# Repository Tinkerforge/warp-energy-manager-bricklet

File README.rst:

WARP Energy Manager Bricklet
============================

This Bricklet together with the ESP32 Ethernet Brick form the
hardware used in the WARP Energy Manager.

See https://www.warp-charger.com/energy-manager.html for more details

This repository contains the firmware source code and the hardware design
files. The documentation generator configs can be found at
https://github.com/Tinkerforge/generators

.. BEGIN WARP REPOSITORIES (managed block, generated from esp32-firmware/repo_overview.rst - do not edit by hand, run update_repo_overview.py instead)

WARP Repositories
-----------------

This is an overview of all repositories that make up the WARP Charger and
WARP Energy Manager ecosystem.

Please report **any** issue concerning WARP hard- or software in the
`esp32-firmware`_ repository, no matter which repository it originates from.

Software
~~~~~~~~

- `esp32-firmware`_ - Source code of the ESP32 firmware shared between all WARP Chargers and Energy Managers

Libraries used by the firmware:

- `tfjson`_ - SAX style JSON serializer and deserializer
- `tfnetwork`_ - Modbus TCP server and client implementation
- `tfocpp`_ - OCPP 1.6 implementation
- `tftools`_ - Miscellaneous tools and helpers

Remote access:

- `esp32-remote-access`_ - Source code of the my.warp-charger.com remote access server

Documentation, tools and integrations:

- `warp-charger`_ - Source code of (docs.)warp-charger.com and the printed manual, released firmwares, datasheets and documents, as well as some tools and hardware design files
- `api.warp-charger.com`_ - Serves APIs that are used by WARP Chargers to obtain relevant public information like day ahead prices
- `vislog.warp-charger.com`_ - Visualizes WARP Charger logs and EVSE debug protocols
- `dbus-warp-charger`_ - Integrates WARP Chargers into a Victron Energy Venus OS device (e.g. Cerbo GX)

WARP Charger Hardware
~~~~~~~~~~~~~~~~~~~~~~

WARP4 Charger
"""""""""""""

*Current charger generation.*

- `warp-esp32-ethernet-v2-brick`_ - Hardware design files of the WARP ESP32 Ethernet Brick 2.0
- `warp-esp32-ethernet-v2-co-bricklet`_ - Firmware source code of the WARP ESP32 Ethernet 2.0 Co Bricklet (co-processor)
- `evse-v4-bricklet`_ - Hardware design files of the EVSE 4.0 Bricklet (firmware shared with the EVSE 2.0 Bricklet)
- `nfc-bricklet`_ - Firmware source code and hardware design files of the NFC Bricklet

WARP3 Charger
"""""""""""""

- `warp-esp32-ethernet-brick`_ - Hardware design files of the WARP ESP32 Ethernet Brick
- `evse-v3-bricklet`_ - Hardware design files of the EVSE 3.0 Bricklet (firmware shared with the EVSE 2.0 Bricklet)
- `nfc-bricklet`_ - Firmware source code and hardware design files of the NFC Bricklet

WARP2 Charger
"""""""""""""

- `esp32-ethernet-brick`_ - Hardware design files of the ESP32 Ethernet Brick
- `evse-v2-bricklet`_ - Firmware source code and hardware design files of the EVSE 2.0 Bricklet
- `nfc-bricklet`_ - Firmware source code and hardware design files of the NFC Bricklet

WARP1 Charger
"""""""""""""

- `esp32-brick`_ - Hardware design files of the ESP32 Brick
- `evse-bricklet`_ - Firmware source code and hardware design files of the EVSE Bricklet
- `rs485-bricklet`_ - Firmware source code and hardware design files of the RS485 Bricklet

WARP Energy Manager Hardware
~~~~~~~~~~~~~~~~~~~~~~~~~~~~~~

WARP Energy Manager 2.0
"""""""""""""""""""""""

*Current energy manager generation.*

- `esp32-ethernet-brick`_ - Hardware design files of the ESP32 Ethernet Brick
- `warp-energy-manager-v2-bricklet`_ - Firmware source code and hardware design files of the WARP Energy Manager 2.0 Bricklet
- `warp-front-panel-bricklet`_ - Firmware source code and hardware design files of the WARP Front Panel Bricklet

WARP Energy Manager 1.0
"""""""""""""""""""""""

- `esp32-ethernet-brick`_ - Hardware design files of the ESP32 Ethernet Brick
- `warp-energy-manager-bricklet`_ - Firmware source code and hardware design files of the WARP Energy Manager Bricklet

Forked/patched projects
~~~~~~~~~~~~~~~~~~~~~~~~~

- `arduino-esp32`_
- `esp32-arduino-libs`_
- `WireGuard-ESP32-Arduino`_

.. Link targets: One definition per repository, keep in sync with the lists above.

.. _esp32-firmware: https://github.com/Tinkerforge/esp32-firmware
.. _tfjson: https://github.com/Tinkerforge/tfjson
.. _tfnetwork: https://github.com/Tinkerforge/tfnetwork
.. _tfocpp: https://github.com/Tinkerforge/tfocpp
.. _tftools: https://github.com/Tinkerforge/tftools
.. _esp32-remote-access: https://github.com/Tinkerforge/esp32-remote-access
.. _warp-charger: https://github.com/Tinkerforge/warp-charger
.. _api.warp-charger.com: https://github.com/Tinkerforge/api.warp-charger.com
.. _vislog.warp-charger.com: https://github.com/Tinkerforge/vislog.warp-charger.com
.. _dbus-warp-charger: https://github.com/Tinkerforge/dbus-warp-charger
.. _warp-esp32-ethernet-v2-brick: https://github.com/Tinkerforge/warp-esp32-ethernet-v2-brick
.. _warp-esp32-ethernet-v2-co-bricklet: https://github.com/Tinkerforge/warp-esp32-ethernet-v2-co-bricklet
.. _evse-v4-bricklet: https://github.com/Tinkerforge/evse-v4-bricklet
.. _nfc-bricklet: https://github.com/Tinkerforge/nfc-bricklet
.. _warp-esp32-ethernet-brick: https://github.com/Tinkerforge/warp-esp32-ethernet-brick
.. _evse-v3-bricklet: https://github.com/Tinkerforge/evse-v3-bricklet
.. _esp32-ethernet-brick: https://github.com/Tinkerforge/esp32-ethernet-brick
.. _evse-v2-bricklet: https://github.com/Tinkerforge/evse-v2-bricklet
.. _esp32-brick: https://github.com/Tinkerforge/esp32-brick
.. _evse-bricklet: https://github.com/Tinkerforge/evse-bricklet
.. _rs485-bricklet: https://github.com/Tinkerforge/rs485-bricklet
.. _warp-energy-manager-v2-bricklet: https://github.com/Tinkerforge/warp-energy-manager-v2-bricklet
.. _warp-front-panel-bricklet: https://github.com/Tinkerforge/warp-front-panel-bricklet
.. _warp-energy-manager-bricklet: https://github.com/Tinkerforge/warp-energy-manager-bricklet
.. _arduino-esp32: https://github.com/Tinkerforge/arduino-esp32
.. _esp32-arduino-libs: https://github.com/Tinkerforge/esp32-arduino-libs
.. _WireGuard-ESP32-Arduino: https://github.com/Tinkerforge/WireGuard-ESP32-Arduino

.. END WARP REPOSITORIES

Repository Content
------------------

software/:
 * examples/: Examples for all supported languages
 * build/: Compiled files
 * src/: Source code of firmware
 * Makefile: Makefile to build project

hardware/:
 * Contains KiCad project files and additionally schematics as PDF

datasheets/:
 * Contains datasheets for sensors and complex ICs that are used

Hardware
--------

The hardware is designed with the open source EDA Suite KiCad
(http://www.kicad.org). Before you are able to open the files,
you have to install the Tinkerforge kicad-libraries
(https://github.com/Tinkerforge/kicad-libraries). You can either clone
them directly in hardware/ or clone them in a separate folder and
symlink them into hardware/
(ln -s kicad_path/kicad-libraries project_path/hardware). After that you
can open the .pro file in hardware/ with KiCad and from there view and
modify the schematics and the PCB layout.

Software
--------

If you want to do your own Brick/Bricklet firmware development we highly
recommend that you use our build environment setup script and read the
tutorial (https://www.tinkerforge.com/en/doc/Tutorials/Tutorial_Build_Environment/Tutorial.html).

To compile the C code we recommend you to install the newest GNU Arm Embedded
Toolchain (https://launchpad.net/gcc-arm-embedded/+download).
You also need to install bricklib2 (https://github.com/Tinkerforge/bricklib2).

You can either clone it directly in software/src/ or clone it in a
separate folder and symlink it into software/src/
(ln -s bricklib_path/bricklib2 project_path/software/src/). Finally make sure to
have CMake installed (http://www.cmake.org/cmake/resources/software.html).

After that you can build the firmware by invoking make in software/.
The firmware (.zbin) can then be found in software/build/ and uploaded
with brickv (click button "Flashing" on start screen).

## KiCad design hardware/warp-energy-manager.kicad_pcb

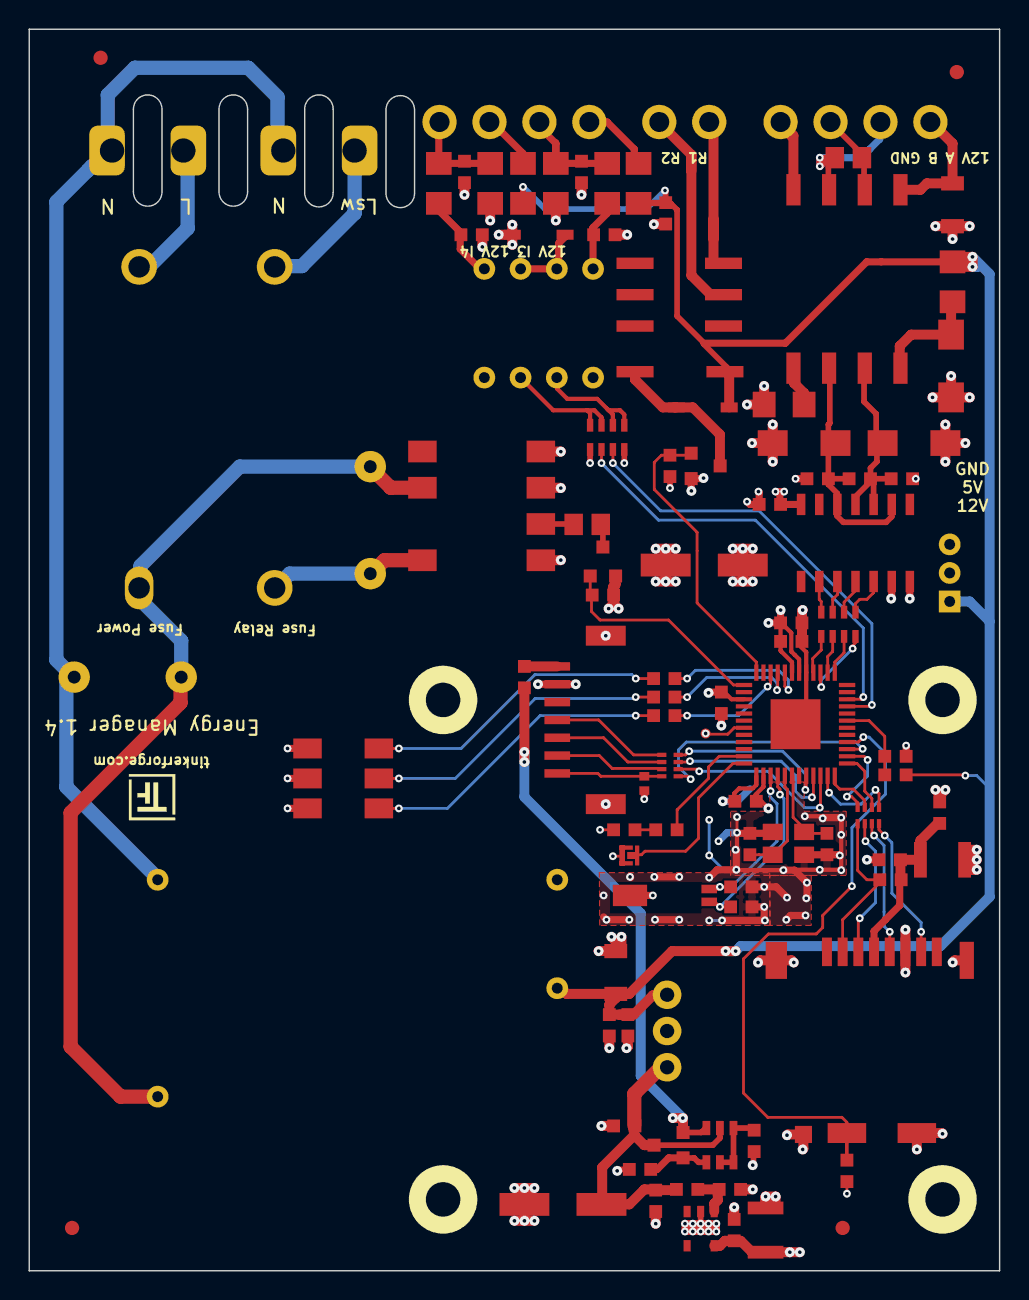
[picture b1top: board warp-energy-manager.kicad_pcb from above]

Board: 4 copper layers, 68.0 x 87.0 mm, 104 parts (0 on the bottom side), 81 nets.

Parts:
A101, A102, A103, A104: DRILL; DRILL_NP_35
C101: 220pF; C0402F
C102, C104, C107, C112, C113, C114, C117, C127, C130, C132: 100nF; C0603F
C103, C106, C124, C125, C126: 1uF; C0603F
C105, C115: 4.7uF/50V; C1206
C108, C109: 100uF; ELKO_63
C110: 2.2uF; C0603F
C111, C116: 100uF; C1210
C118, C119: 15pF; C0603F
C128, C129: 10pF; C0603F
C131: 220nF; C0603F
D101: CLP6C-FKB-CK1P1G1BB7R3R3; PLCC6-6x5
D102, D106, D111: SMAJ12CA; DO-214AC
D103: blue; D0603F
D105, D107: B0520LW-7; SOD-123
F101, F102: FUSE; Fuse-Holder-5x20
Fiducial_Mark: VAL**; Fiducial_Mark
Fiducial_Mark#2, Fiducial_Mark#3, Fiducial_Mark#4: VAL**; Fiducial_Mark
J101: Boot; SolderJumper
J102: DM3CS; SD-Card-DM3CS
L101, L102, L103: FB; R0603F
L104: WE-SL
P101: CON-SENSOR2; CON-SENSOR2_180
P102: Relay; OQ_2P_5mm_230V
P103: L+N; OQ_2P_5mm_230V
P104: OUT; OQ_2P
P105: INPUT; OQ_4P
P106: DNP; JST-PH-3-THT
P110: MODBUS; OQ_4P
P111: Debug; DEBUG_PAD
PTC101, PTC102: PTC 0.45A; R1206E
Q102: SI2305CDS-T1-GE3; SOT23GDS
Q103: 2N7002P; SOT23GDS
Q105: SSM3J355R,LF; SOT23GDS
R101, R102: 51; R0603F
R103: 100; R0603F
R104, R105, R111, R112, R116, R117: 1k; R1206E
R106, R109, R140: 10k; R0603F
R107: 300k; R0603F
R108: 100k; R0603F
R113, R128: MOV-10D391KTR; VAR_10mm
R114, R137: 120; R0805E
R115, R118, R124: 1k; R0603F
R133: 47k; R0603F
R134, R136: 750; R0603F
R135: DNP; R0603F
REL101: AGQ200S12Z; AGQ2X0
RP101, RP103: 82; 4X0402
RP102: 10k; 0603X4
RP105: 10k; 4X0603
U101: XMC1404; QFN48-EP2
U103: DMMT5401; SOT26
U108: AQH3213AX; AQ-H
U109: HCPL2731; DIP-8
U110: TPS70933DBVR; SOT23-5
U111: IRM02-12; IRM02
U112: WPMDL110
U113: SP3491; SOIC-14_3.9x8.7mm_Pitch1.27mm
X101: 16MHz; CRYSTAL_3225
X102: 32.768kHz; AB26TRQ

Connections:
3V3: C102.1, C109.1, C110.1, C111.1, C127.1, C130.1, C131.1, C132.2, D101.1, D101.2, D101.3, D103.1, L102.2, Q102.S, R106.2, R115.2, R134.1, RP105.1, RP105.4, U101.18, U101.19, U101.27, U101.38, U109.8, U110.5, U113.14
5V: C103.1, C108.1, C126.1, L101.2, P106.2, Q105.D, U103.5, U112.3
485-D: RP102.4, U101.15
485-DE: RP102.3, U101.13
485-R: RP102.1, U101.16
485-~REB: RP102.2, U101.14
BOOT: J101.2, U101.36
GND: C101.2, C102.2, C103.2, C104.2, C105.2, C106.2, C107.2, C108.2, C109.2, C110.2, C111.2, C112.2, C113.1, C114.2, C115.1, C116.2, C117.2, C118.1, C119.1, C124.2, C125.2, C126.2, C127.2, C128.2, C129.2, C130.2, C131.2, C132.1, D102.1, D105.2, D106.2, D111.2, J101.1, J102.6, J102.S, P101.2, P101.EP, P106.3, PTC101.2, Q103.S, R104.2, R105.2, R108.1, R118.1, R133.1, R136.2, R140.1, U101.17, U101.37, U101.EP, U108.1, U108.3, U108.4, U109.5, U110.2, U111.4, U112.2, U113.6, U113.7, X101.3, X102.3
IN0: RP105.2, U101.9
IN1: RP105.3, U101.10
L: F101.2, R113.2, R128.1, U108.6, U111.1
N: P102.2, P103.2, R128.2, U111.2
unnamed: C101.1, P101.7, RP101.4
unnamed: C104.1, P105.2, R104.1, R112.1
unnamed: C106.1, L101.1, U110.1
unnamed: C107.1, P105.4, R105.1, R117.1
unnamed: C112.1, R117.2, U109.4
unnamed: C114.1, R112.2, U109.1
unnamed: C115.2, L104.5, P110.1
unnamed: C116.1, C117.1, J102.4, L102.1, R109.2
unnamed: C128.1, U101.41, X101.2
unnamed: C129.1, U101.42, X101.1
unnamed: D101.4, R101.1
unnamed: D101.5, R102.1
unnamed: D101.6, R103.1
unnamed: D102.2, L104.4, PTC102.2
unnamed: D103.2, R124.2
unnamed: D105.1, U109.2, U109.3
unnamed: D106.1, L104.3, R135.2, R136.1, U113.10, U113.11
unnamed: D107.1, Q103.D, REL101.8
unnamed: D111.1, L104.2, R134.2, R135.1, U113.9, U113.12
unnamed: F101.1, P103.1
unnamed: F102.1, P102.1
unnamed: F102.2, R113.1, U108.8
unnamed: J102.2, R109.1, RP103.1
unnamed: J102.3, RP103.2
unnamed: J102.5, RP103.3
unnamed: J102.7, RP103.4
unnamed: L103.1, Q105.S, U103.6
unnamed: L103.2, P101.1
unnamed: L104.1, PTC101.1
unnamed: L104.6, P110.3, R137.1
unnamed: L104.7, P110.2, R137.2
unnamed: L104.8, P110.4
unnamed: P101.4, RP101.1
unnamed: P101.5, RP101.2
unnamed: P101.6, RP101.3
unnamed: P104.1, REL101.4
unnamed: P104.2, REL101.3
unnamed: P105.1, R111.1
unnamed: P105.3, R116.1
unnamed: P111.1, U101.31
unnamed: Q102.D, R114.1
unnamed: Q105.G, R133.2, U103.1
unnamed: R101.2, U101.22
unnamed: R102.2, U101.21
unnamed: R103.2, U101.20
unnamed: R114.2, U108.2
unnamed: R124.1, U101.35
unnamed: R140.2, U103.2, U103.3, U103.4
unnamed: RP102.5, U113.5
unnamed: RP102.6, U113.4
unnamed: RP102.7, U113.3
unnamed: RP102.8, U113.2
unnamed: RP105.5, RP105.6, U109.6
unnamed: RP105.7, RP105.8, U109.7
OUT: Q103.G, R118.2, U101.24
RELAY: Q102.G, R115.1, U101.25
RTC-XTAL1: C119.2, U101.39, X102.2
RTC-XTAL2: C118.2, U101.40, X102.1
S-CLK: RP101.7, U101.45
S-CS: RP101.8, U101.44
S-MISO: RP101.5, U101.3
S-MOSI: RP101.6, U101.46
SD-CDS: J102.CDS, R106.1, U101.4
SD-CLK: RP103.6, U101.1
SD-CS: RP103.8, U101.2
SD-MISO: RP103.5, U101.47
SD-MOSI: RP103.7, U101.48
V12: R107.1, R108.2, U101.7
VCC: C105.1, C113.2, C124.1, C125.1, D107.2, P106.1, PTC102.1, R107.2, R111.2, R116.2, REL101.1, U111.3, U112.1

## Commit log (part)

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2021-10-11 add hardware files
2021-10-12 changed info box
2021-10-12 changed RS485 resistors
2021-10-13 Add initial stub firmware implementation
2021-10-13 Add drivers for IO, SDM630 and input voltage
2021-10-13 version 1.1
    * fix relay pinning
    * fix ac/dc power supply position
2021-10-14 Implement relative energy feature
2021-10-25 Update KiCad link
    https://www.kicad.org/blog/2021/10/Avoid-links-to-former-kicad-domain/
2021-11-02 enlarged esp holes
2021-11-04 finish version 1.2
    * move elko
    * change rs485 resistors
    * design improvements
2021-12-16 add version 1.3
    * add 12V output for rs485
    * change protection diodes type
2021-12-17 drc check
2022-01-18 generate production version
    add fiducials
2022-03-23 add version 1.4
    add micro sd card socket
2022-03-24 add 32.768kHz crystal for rtc
2022-03-24 specify rtc capacitors
2022-04-01 fix routing
2022-05-04 Add support for SDM72V2, add initial SD card tests
2022-06-02 Add initial implementation of SDM630/SDM72V2 simulator
    This will be used for WARP Energy Manager testing
2022-07-06 Add license files.
2022-08-10 Add better defaults
2022-08-10 Add charger simulator and tester ui
2022-08-11 Use improved SDM meter detection code (from EVSE V2)
2022-08-23 Remove unused input configuration
2022-08-23 Implement contactor check
2022-08-23 Remove unused input configuration element in struct
2022-09-23 Whitespace
2022-09-23 Ignore generated PyQt UI files
2022-12-16 Implement new charge manager protocol in simulator.
2022-12-16 Fix copy+paste error
    Accidentally used get_contactor instead of get_state
    in get_all_data_1 for state
2022-12-19 simulator: Integrate meter simulator.
2022-12-22 Fix active high/low mixup
2022-12-23 simulator: Report CP disconnect feature, fix zero meter values.
    - Report support for CP disconnect to manager.
    - Make current allocated by manager available to simulator.
    - Fix default value being used in meter simulator when power should be zero.
2023-01-13 simulator: Fix SDM simulator consumption scaling.
2023-01-16 Remove fatfs and DAVE implementation for SPI/FATFS/RTC
2023-01-16 Add support for SDM72CTM
2023-01-16 Add initial sd card support with littlefs testing
    We switched from fatfs and the DAVE sdmmc implementation from
    Infineon to our own sdmmc implementation and littlefs.
    The Infineon lib was not stable and to complex to debug...
    Note: Littlefs currently consists of testing code, this is
    still WIP
2023-01-16 Add sdmmc file headers
2023-01-17 Add support for SDMMC CID/CSD
2023-01-17 Remove unused code
2023-01-17 Add proper sdmmc error handling
2023-01-17 Update bindings
2023-01-17 Use 20MHz as SD MMC default speed for now
2023-01-17 Add select comment
2023-01-17 Return cid/csd error if they occur
2023-01-17 Fix indentation
2023-01-19 Add support for new SD API
2023-01-30 Use coop task and fifo/interrupts for more efficient sdmmc handling
2023-01-30 Change contactor check pin to active low
2023-01-30 Implement getter/setter/callbacks for new API
2023-01-30 check with 1 as max length for daily data
2023-01-31 Check if old message is buffered before check for new message
2023-01-31 Check date directly in getter/setter
2023-01-31 Add support for daily wallbox data point
2023-01-31 Improve error logging and handling
2023-01-31 Add support for error during async transceive
2023-01-31 Increase coop task stack size
2023-01-31 Add support for Energy Manager data
2023-01-31 Add test that writes/reads one month for 2 wb and em
2023-01-31 Add additional yields in sd code
2023-02-02 Use local pointer to save the time for accessing the struct
2023-02-02 Add one yield per read/write
2023-02-02 Make sure rs485 IRQs has lower priority than sdmmc IRQs
2023-02-02 Set sd status at the end of initialization
    to make sure that everything is completely initialized
    before any other code tries to access the sd card
2023-02-02 Improve SD error and hotplug handling
2023-02-02 Make spaces/tabs consistenet
2023-02-02 Improve test script logging
2023-02-06 Add support to format sd card through API
2023-02-10 Add support for SDM630MCTV2
2023-02-10 Make sure errors are unique
2023-02-15 Add sd error code for "no sd card"
2023-02-15 Make formating more consistent
2023-02-15 Move "error no card"-detection below hot-remove detection
    Otherwise we overwrite the status too early.
2023-02-20 Change wallbox id from uint8 to uint32
    This way the Brick can use the UID. We also save the filename
    as Base58 now to reduce the file size and make it human readable.
2023-02-20 Use correct encode offset
2023-02-20 Add additional contactor check debounce
2023-02-20 Add support for Set/GetDateTime
    TODO: In date_time init we still need to check if the time is already
    set and not re-set it in this case.
2023-02-23 Make sure RTC is not reconfigured if it is already running
2023-02-24 move to kicad6
2023-02-24 remove old lib path
2023-02-27 Add lfs filesystem mount script
2023-02-28 Change version to release version number
2023-02-28 Turn logging off
2023-02-28 Add ref for 2.0.0
2023-02-28 Sanity check amount in 5min/daily data getter
2023-03-02 Change contactor check from input 3 to input 4
2023-03-02 Add GetUptime API
2023-03-02 Improve sd card read performance
    Use a buffered read that does not open/close the file for each chunk
2023-03-02 Add date and ref for 2.0.1
2023-03-02 Fix copy+paste error
2023-03-02 Change version back to 2.0.0 and change flash from 64kb to 200kb
    We had a big fuckup and released firmwares with max 64kb flash
    while we have a mcu with 200kb flash. The old firmwares are incompatible
    because of CRC at end of flash.
2023-03-07 Add support for new LEDState-API
    Blinking and Breathing is based on the same timing as the WARP Charger LED
2023-03-09 Add orange LED blinking if connection lost
2023-03-09 Improve new file handling
    Read empty new files from flash instead of RAM
2023-03-09 Change connection lost interval to 10s
2023-03-16 Add changelog for 2.0.1
2023-03-21 Initialize meter values with NaN
    and only set meter type after all vales have been read at least once
2023-03-21 Check if config is set for external 32.768 kHz crystal
    We had a bug in early bootloader versions that did not set it correctly,
    so we re-set it in this case in the date_time_init function
2023-03-22 Make sure that each_value_read_once is always marked correctly
2023-03-23 README: Remove development hint, add some details
2023-04-13 Add support for Get/SetDataStorage
    Internal persistant storage that can be used by Brick.
    Maximum sd write interval is 10 minutes.
2023-04-27 Fix compilation when math.h providles logf.
    On some system, math.h declares logf, which collides with the logf macro
    from logging.h. Rename the unused logf from math.h to avoid the collision.
2023-05-17 Improve real-time-clock initialization
    old code sometimes was so slow that the watchdog triggered
2023-05-17 Add rev for 2.0.2 to changelog
2023-06-13 Make sure meter type is only reconfigured once per complete read of register set
2023-06-15 Move meter functionality bricklib2/warp
    This is now shares wid EVESE Bricklet 2.0
2023-06-21 Update changelog for changes in bricklib
2023-06-21 Add date and ref for 2.0.3
2023-08-14 Increase LED connection lost time to 15s and use during start-up.
    The WEM Brick takes at least 10s to start after a power-on reset,
    so give it 15s to avoid confusing users with orange blinking
    because of an expected delay.
2023-09-01 Fix typos in changelog
2023-09-01 Add 3rd data storage page
2023-09-01 Update changelog
2023-10-26 Add date and ref for 2.0.4 release
2023-10-27 Use new unified meter implementation from bricklib2
2023-10-27 Change "fast read" meter values to power and current per phase
2023-12-08 Add support for resetable relative import/export energy
2024-01-23 Add date and ref for 2.0.5
2024-06-05 Prepare to add math support (not used currently)
2024-06-05 Fix name changes
2024-06-05 Add initial 2.0.6 changelog entry
2024-09-02 Move everything that is common between WEM 1/2 to bricklib2
2024-09-02 Add price to Energy Manager data point
2024-09-02 Add support for price data
    sd write/read changes in bricklib2
2024-09-02 Move EEPROM and voltage code to bricklib
2024-09-13 Move detect pin definition to config_sdmmc.h
    It was in the sd.h before, but that one is shared between
    WEM1 and WEM2 now.
2024-09-17 Use new cb length defines (from bricklib)
2024-09-19 Fix cb sizes (new sizes because of price data)
2024-10-14 Add random tests and update bindings
2024-10-25 Add support for status parameter in get_data_storage
2024-10-28 Initialize data storage before sd card
2024-11-28 Add date and ref for v2.0.6
2025-02-05 Make sure first set_data_storage call is always written to SD card
2025-02-05 Add ref for 2.0.7
2025-03-28 Update changelog and version
2025-03-28 Add ref for 2.0.8
2025-04-03 Increase data storge pages from 3 to 5 (through bricklib2)
2025-04-03 Add ref for 2.0.9
2025-07-16 README: Add repo overview.
2025-09-14 Add support for DMED341MID7ER, DSZ16DZE, WM3M4C and use restructured meter code
    see bricklib2 for implementation
2025-09-16 Rename MeterRegisterType to use the same name as in esp32 firmware
2025-09-16 Add libm and free some RAM to allow sqrt use in bricklib2
2025-09-21 Make cmake version compatible to new build environment
2025-09-21 Add support for dynamic length meter values
2025-10-02 Fix -Wextra warnings and add new warning flags introduced in EVSE V2
2025-11-03 Add ref and release date for 2.0.10
2026-05-13 Add support for WM3M4, update changelog
2026-05-13 Add ref for 2.0.11

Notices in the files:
hardware/warp-energy-manager.kicad_pcb:
Licensed under CERN OHL v.1.1
Copyright (©) 2022, B.Nordmeyer
Copyright Tinkerforge GmbH 2022.
This documentation describes Open Hardware and is licensed under the
CERN OHL v. 1.1.
